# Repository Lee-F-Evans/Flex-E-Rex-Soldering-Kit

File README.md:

<header>
    <h1 align = "center">Flex-E-Rex-Soldering-Kit</h1>
</header>

## About
Flex E Rex is a beginer friendly soldering project developed as educational content within the Schulich School of Engineering Makermuliplex and Zetta by Lee Evans and Connor McNeill. The contents of this repo allow for anyone to assemble these kits for themselves.

For more information about equipment, trainings and classes offered within the Makermultiplex visit https://schulich.libguides.com/m2z/. 

## How to Use
To get the kits ready for use you will need to order PCBs, 3D print the 2 enclosure parts, order the circuit components listed in the "Parts" section or found in the BOM, gather required tools and print the instructions sheet if needed.

It is recommended to briefly review the instructions before beginning assembly! The order of stems and LED spacing are important.

## Parts and Tools

### Tools:
- Soldering iron
- Lead Free Solder
- Flush cuts/Wire cutters

### Parts:
Details and links to the following components can be found in the BOM excel sheet.

| Part | Quantity |
| ----------- | ----------- |
| LED | 2 |
| Switch (PN:1825232-1) | 1 |
| Coin cell holder (PN: BK-913)|1|
|0 ohm resistor|2|
|PCB|1|
|Dino Head Top|1|
|Dino Head Bottom and Body |1|
|CR2032 coin cell battery|1|

## Fabricating PCBs

All files for fabrication are found in the folder `Flex-E Rex PCB Files 1_4x`. The fab files for different versions present as `Gerber and Drill Files_Rev#`. It is recomended to use the highest revision number as earlier versions may have problems.

Order more than you need! The highest expense when ordering these boards is shipping, so adding a few extra to the cart wont hurt.

### How We Ordered Our Boards 
- We used JLCPCB.com for fabrication, but any PCB fabricator should be able to produce these boards. 
- The boards are `1.6mm` thick.
- Base material is `FR4`.
- Surface finish is `lead free HASL`.
- Order number uses a `specified location`.
- All other settings were left as default.

## Printing Parts

Most recent STL or .3mf files are found in `Flex-E Rex CAD Files 1_4x\MK2.2.X\STL`. You will need to print both `MK2.2.0 Head+Body Assy.STL` and `MK2.2.2 Head Top.STL` for a single kit. If higher versions of the model are present, use those.

We use Prusa printers and Prusa Slicer for producing our parts, but any calibrated 3D printer and slicing software will work. Below are the settings we use. 
- PLA for material
- 0.4mm diameter nozzle
- 0.2mm layer height
- 15% infill
- No supports
- No brim/raft
   
## Versioning Explained
It is always recommended to use the highest versioned PCB and enclosure files. The below information is just to explain the versioning system used. 

**#.X.X** - Indicates assembly versions. Mostly variations in size or major design changes.

**X.#.X** - Indicates PCB versions. This can be found on the back of the PCB as a "V0.X" needs to match the enclosure parts. 

**X.X.#** - Indicates eclosure part versions. 

**Note:** Any parts with matcing #.#.X versions will be compatible.

Example: *2.2.1* is assembly version 2 with PCB version 2 and enclosure parts version 1.

## Attributions
The model design for Flex-E Rex has been adapted from various remixed models originally starting from `zheng3`'s Robber Rex https://www.thingiverse.com/thing:613445. 

Thank you Kevin, Sean, and Allyne from MakerMultiplex for feedback and support on this project.

## Licencing
The enclosure parts for this project are considered a remix of the original and are licenced under [Creative Commons Share Alike Licence](https://creativecommons.org/licenses/by-sa/4.0/legalcode.en) 

The PCB design, instructions and other content relating to the soldering kit are original designs and are licenced under [Attribution NonCommercial Share Alike (CC BY-NC-SA)](https://creativecommons.org/licenses/by-nc-sa/4.0/)

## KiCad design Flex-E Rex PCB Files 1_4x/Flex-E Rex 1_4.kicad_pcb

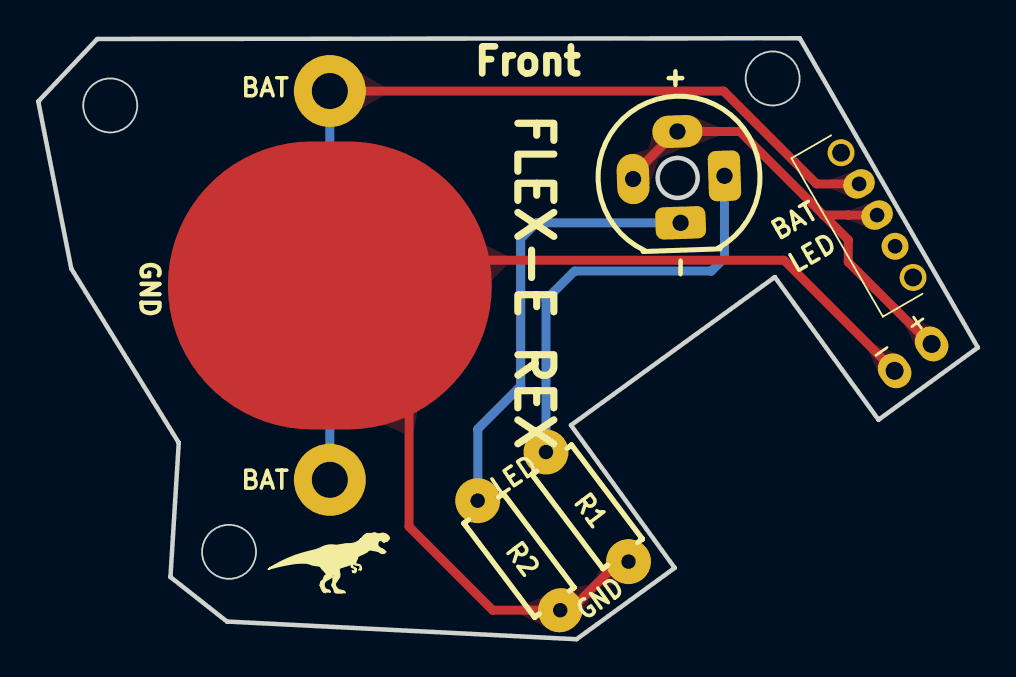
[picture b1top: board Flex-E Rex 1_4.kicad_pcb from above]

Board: 2 copper layers, 52.2 x 33.4 mm, 7 parts (1 on the bottom side), 5 nets.

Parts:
BT1: BK-913; BAT_BK-913
D1, D2: LED; LED_D8.0mm-3
J1: Conn_01x02_Pin; PinHeader_1x02_P2.54mm_Vertical
R1, R2: R; R_Axial_DIN0207_L6.3mm_D2.5mm_P7.62mm_Horizontal
SW1: 1825232-1; 1825232-1_TEC

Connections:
+3V0: D1.3, D2.3, J1.1, SW1.2
GND: BT1.-, J1.2, R1.2, R2.2
unnamed: BT1.S+1, BT1.S+2, SW1.3
unnamed: D1.1 (K), R2.1
unnamed: D2.1 (K), R1.1

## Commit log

2024-01-22 Added first set of files
    Missing CAD models. Will add later after some changes by Connor.
2024-01-22 made small changes
2024-01-22 Connor Adding CAD Files
2024-01-22 updated led pin to be more sturdy
2024-01-23 Further LED Pin revisions
2024-01-24 Revision formatting change + Head print fix
2024-01-25 Updating readme
2024-01-25 Changed PCB version ID to X.X.X format
2024-01-25 test
2024-01-29 Update README.md
    Test to resolve images not appearing in README
2024-01-29 updated to_do and testing merge
2024-01-29 testing github view of images
2024-01-29 Increased thickness of head rear wall
2024-01-29 added gifs and formatting
2024-01-29 more formatting
2024-02-02 Updated clasp tolerances and LED/eye hole tolerances
2024-02-03 eye hole dia. set to 5.25mm
2024-02-07 finished first complete draft of the README
2024-02-08 removed to-dos
2024-03-08 Added first set of files
    Missing CAD models. Will add later after some changes by Connor.
    made small changes
    Connor Adding CAD Files
    updated led pin to be more sturdy
    Further LED Pin revisions
    updated README
2024-03-13 added new PCB version. Increased size of pads and flipped the solder pad side for the LEDs
